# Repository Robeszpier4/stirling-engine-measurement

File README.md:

Ezen NYÁK lap (Nyomtatott áramköri lap) egy strling motor frekvenicájának és a két lapja közötti hőmérséklet különbség mérésére készült. 3 darab feszültségosztón alapuló termisztoros hőmérsékletmérő került elhelyezésre (ezek közül kettő a két lap hőmérsékletét és egy a környezet hőmérsékletét méri), melyeket egy Raspberry Pi Pico 2 ADC-je (Analog to digital converter) olvas ki. Továbbá egy a mikrokontrollerre kötött rés-opto modullal méri a berendezés a Striling motor frekvenciáját. A NYÁK-ra elhelyezésre került 2 darab LED is, melyet a mérés során különböző a mérést elősegítő feladatokra lehet használni.

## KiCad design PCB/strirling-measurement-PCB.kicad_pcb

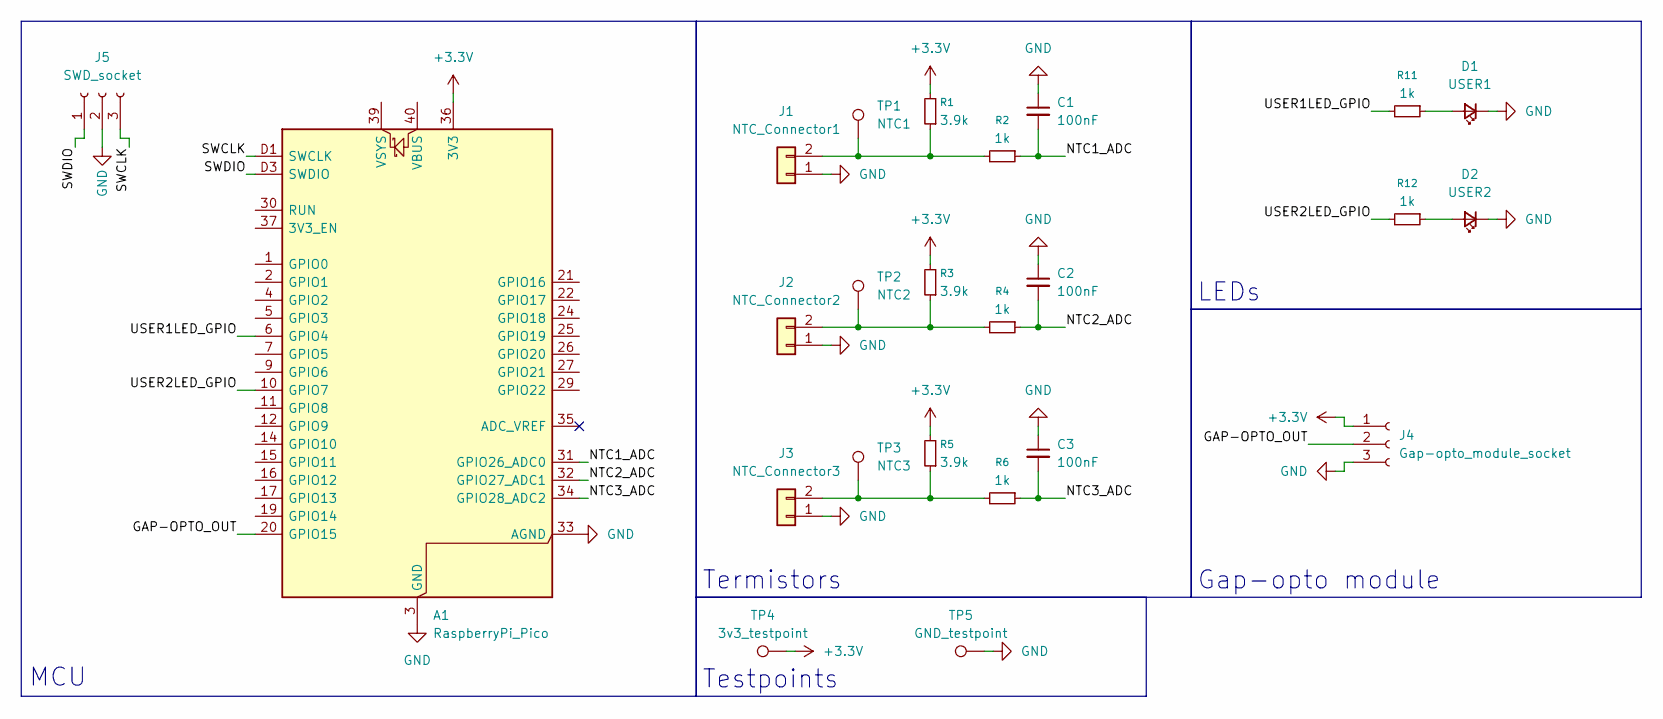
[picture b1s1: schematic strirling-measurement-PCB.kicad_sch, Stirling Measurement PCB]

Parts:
A1: RaspberryPi_Pico; RaspberryPi_Pico_SMD_HandSolder
C1, C2, C3: 100nF; C_0402_1005Metric
D1: USER1; LED_D5.0mm
D2: USER2; LED_D5.0mm
J1: NTC_Connector1; JST_S2B-ZR_LF__SN_
J2: NTC_Connector2; JST_S2B-ZR_LF__SN_
J3: NTC_Connector3; JST_S2B-ZR_LF__SN_
J4: Gap-opto_module_socket; gap-opto_module
J5: SWD_socket; swd_header
R1, R3, R5: 3.9k; R_0603_1608Metric
R2, R4, R6: 1k; R_0402_1005Metric
R11, R12: 1k; R_0805_2012Metric
TP1: NTC1; TestPoint_Pad_2.0x2.0mm
TP2: NTC2; TestPoint_Pad_2.0x2.0mm
TP3: NTC3; TestPoint_Pad_2.0x2.0mm
TP4: 3v3_testpoint; TestPoint_Pad_2.0x2.0mm
TP5: GND_testpoint; TestPoint_Pad_2.0x2.0mm

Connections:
+3.3V: A1.36 (3V3), J4.1, R1.2, R3.2, R5.2, TP4.1 (1_1)
/GAP-OPTO_OUT: A1.20 (GPIO15), J4.2
/NTC1_ADC: A1.31 (GPIO26_ADC0), C1.2, R2.1
/NTC2_ADC: A1.32 (GPIO27_ADC1), C2.2, R4.1
/NTC3_ADC: A1.34 (GPIO28_ADC2), C3.2, R6.1
/SWCLK: A1.D1 (SWCLK), J5.3
/SWDIO: A1.D3 (SWDIO), J5.1
/USER1LED_GPIO: A1.6 (GPIO4), R11.2
/USER2LED_GPIO: A1.10 (GPIO7), R12.2
GND: A1.3 (GND), A1.8 (GND), A1.13 (GND), A1.18 (GND), A1.23 (GND), A1.28 (GND), A1.33 (AGND), A1.38 (GND), A1.D2 (GND), C1.1, C2.1, C3.1, D1.1 (K), D2.1 (K), J1.1, J2.1, J3.1, J4.3, J5.2, TP5.1 (1_1)
unnamed: D1.2 (A), R11.1
unnamed: D2.2 (A), R12.1
unnamed: J1.2, R1.1, R2.2, TP1.1 (1_1)
unnamed: J2.2, R3.1, R4.2, TP2.1 (1_1)
unnamed: J3.2, R5.1, R6.2, TP3.1 (1_1)

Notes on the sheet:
Gap-opto module
Testpoints
MCU
Termistors
LEDs

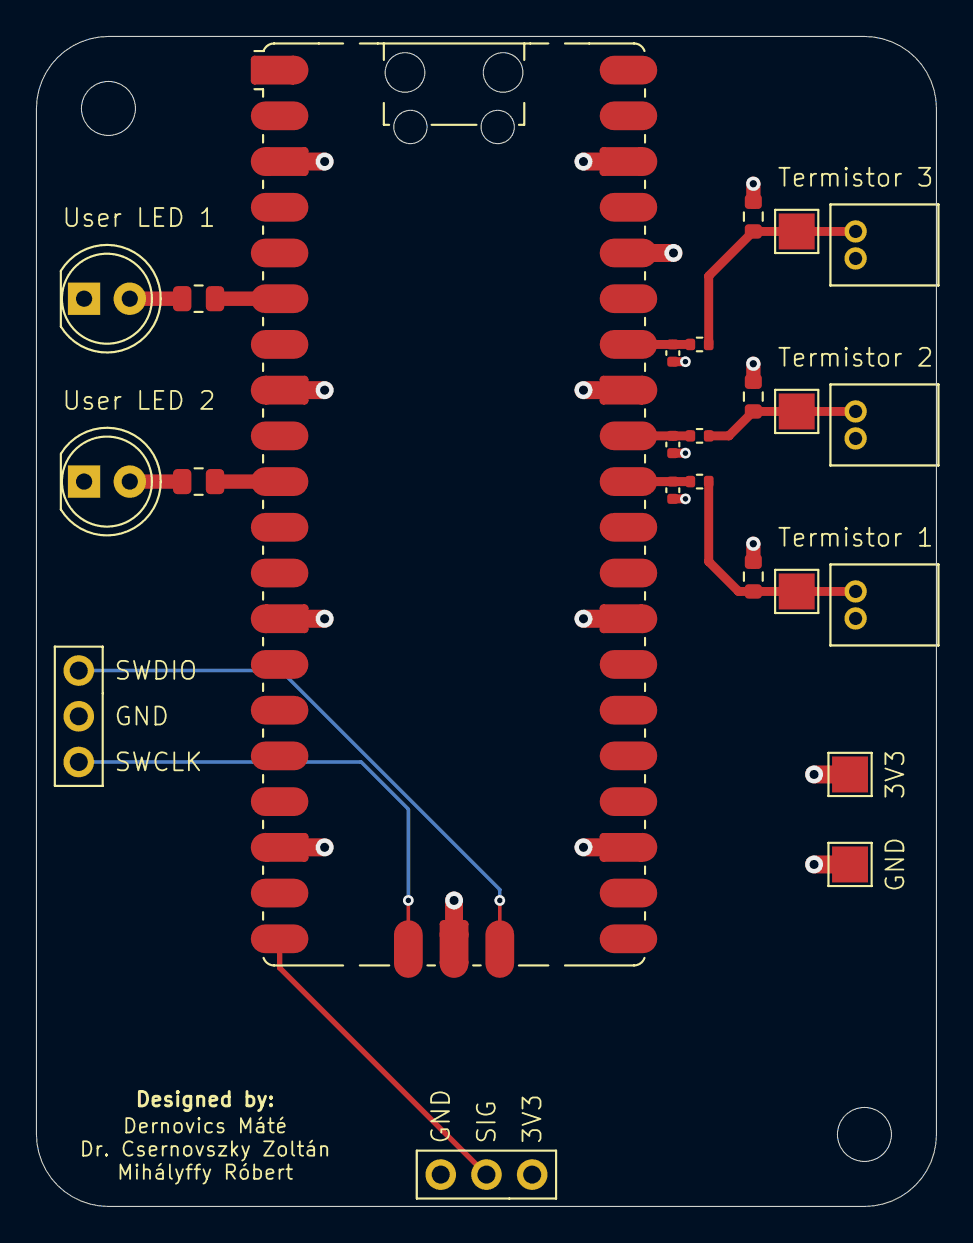
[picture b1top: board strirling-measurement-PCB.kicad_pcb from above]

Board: 4 copper layers, 50.0 x 65.0 mm, 24 parts (0 on the bottom side), 15 nets.
